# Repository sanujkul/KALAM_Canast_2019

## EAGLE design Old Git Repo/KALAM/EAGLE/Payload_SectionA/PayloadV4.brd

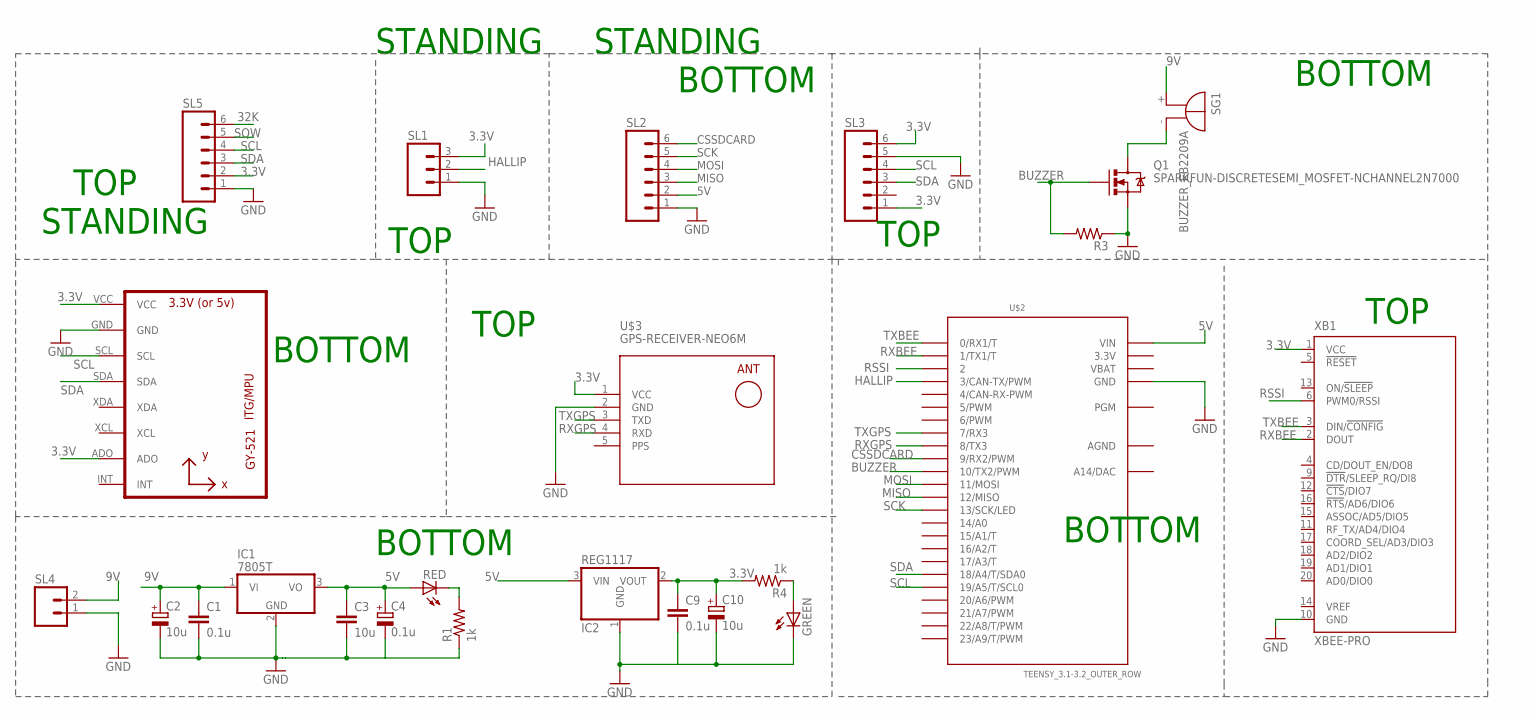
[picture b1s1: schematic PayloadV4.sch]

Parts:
C1, C9: 0.1u; C025-025X050
C2, C10: 10u; E2,5-6
C3: 10u; C025-025X050
C4: 0.1u; E2,5-6
GREEN: red; LED3MM
IC1: 7805T; TO220H
IC2: REG1117; SOT223
Q1: SPARKFUN-DISCRETESEMI_MOSFET-NCHANNEL2N7000; SPARKFUN-DISCRETESEMI_TO-92
R1, R4: 1k; 0204/7
R3: R-US_0204/7; 0204/7
RED: red; LED3MM
SG1: BUZZER_EB2209A
SL1: M03; 03P
SL2, SL3, SL5: M06; 06P
SL4: M02; 02P
U1: GY-521MPU6050; GY-521
U$2: TEENSY_3.1-3.2_OUTER_ROW; TEENSY_3.0-3.2&LC_OUTER_ROW
U$3: GPS-RECEIVER-NEO6M
XB1: XBEE-PRO

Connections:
3.3V: C9.1, C10.+, IC2.2 (VOUT), R4.2, SL1.3, SL3.1, SL3.6, SL5.2, U1.ADO, U1.VCC, U$2.3.3V, U$2.3.3V1 (3.3V), U$3.1 (VCC), XB1.1 (VCC)
5V: C3.1, C4.+, IC1.3 (VO), IC2.3 (VIN), RED.A, SL2.2, U$2.VIN
9V: C1.1, C2.+, IC1.1 (VI), SG1.+, SL4.2
32K: SL5.6
AGND: U$2.AGND
BUZZER: Q1.2 (G), R3.2, U$2.10 (10/TX2/PWM)
CSSDCARD: SL2.6, U$2.9 (9/RX2/PWM)
GND: C1.2, C2.-, C3.2, C4.-, C9.2, C10.-, GREEN.K (C), IC1.2 (GND), IC2.1 (GND), Q1.1 (S), R1.1, R3.1, SL1.1, SL2.1, SL3.5, SL4.1, SL5.1, U1.GND, U$2.GND, U$2.GND1 (GND), U$3.2 (GND), XB1.10 (GND)
HALLIP: SL1.2, U$2.3 (3/CAN-TX/PWM)
MISO: SL2.3, U$2.12 (12/MISO)
MOSI: SL2.4, U$2.11 (11/MOSI)
unnamed: R1.2, RED.K (C)
unnamed: GREEN.A, R4.1
unnamed: Q1.3 (D), SG1.-
PPS: U$3.5 (PPS)
RSSI: U$2.2, XB1.6 (PWM0/RSSI)
RXBEE: U$2.1 (1/TX1/T), XB1.2 (DOUT)
RXGPS: U$2.8 (8/TX3), U$3.4 (RXD)
SCK: SL2.5, U$2.13 (13/SCK/LED)
SCL: SL3.4, SL5.4, U1.SCL, U$2.19/A5 (19/A5/T/SCL0)
SDA: SL3.3, SL5.3, U1.SDA, U$2.18/A4 (18/A4/T/SDA0)
SQW: SL5.5
TXBEE: U$2.0 (0/RX1/T), XB1.3 (DIN/!CONFIG)
TXGPS: U$2.7 (7/RX3), U$3.3 (TXD)
VBAT: U$2.VBAT

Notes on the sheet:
TOP
BOTTOM
STANDING

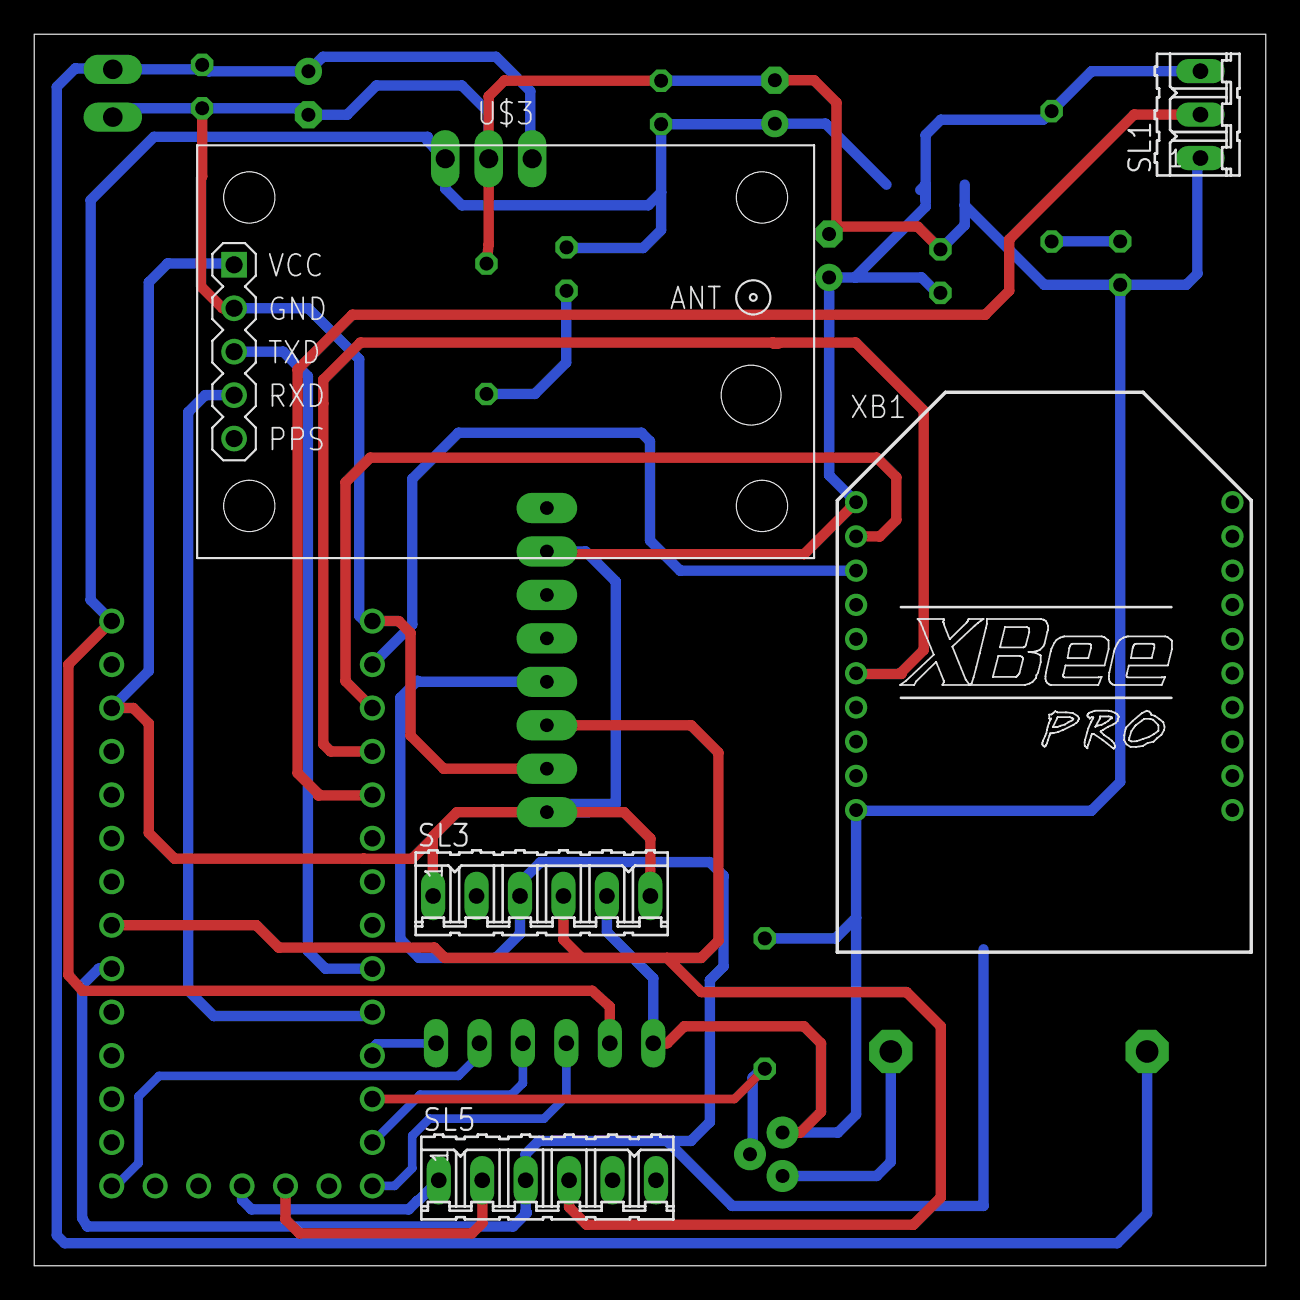
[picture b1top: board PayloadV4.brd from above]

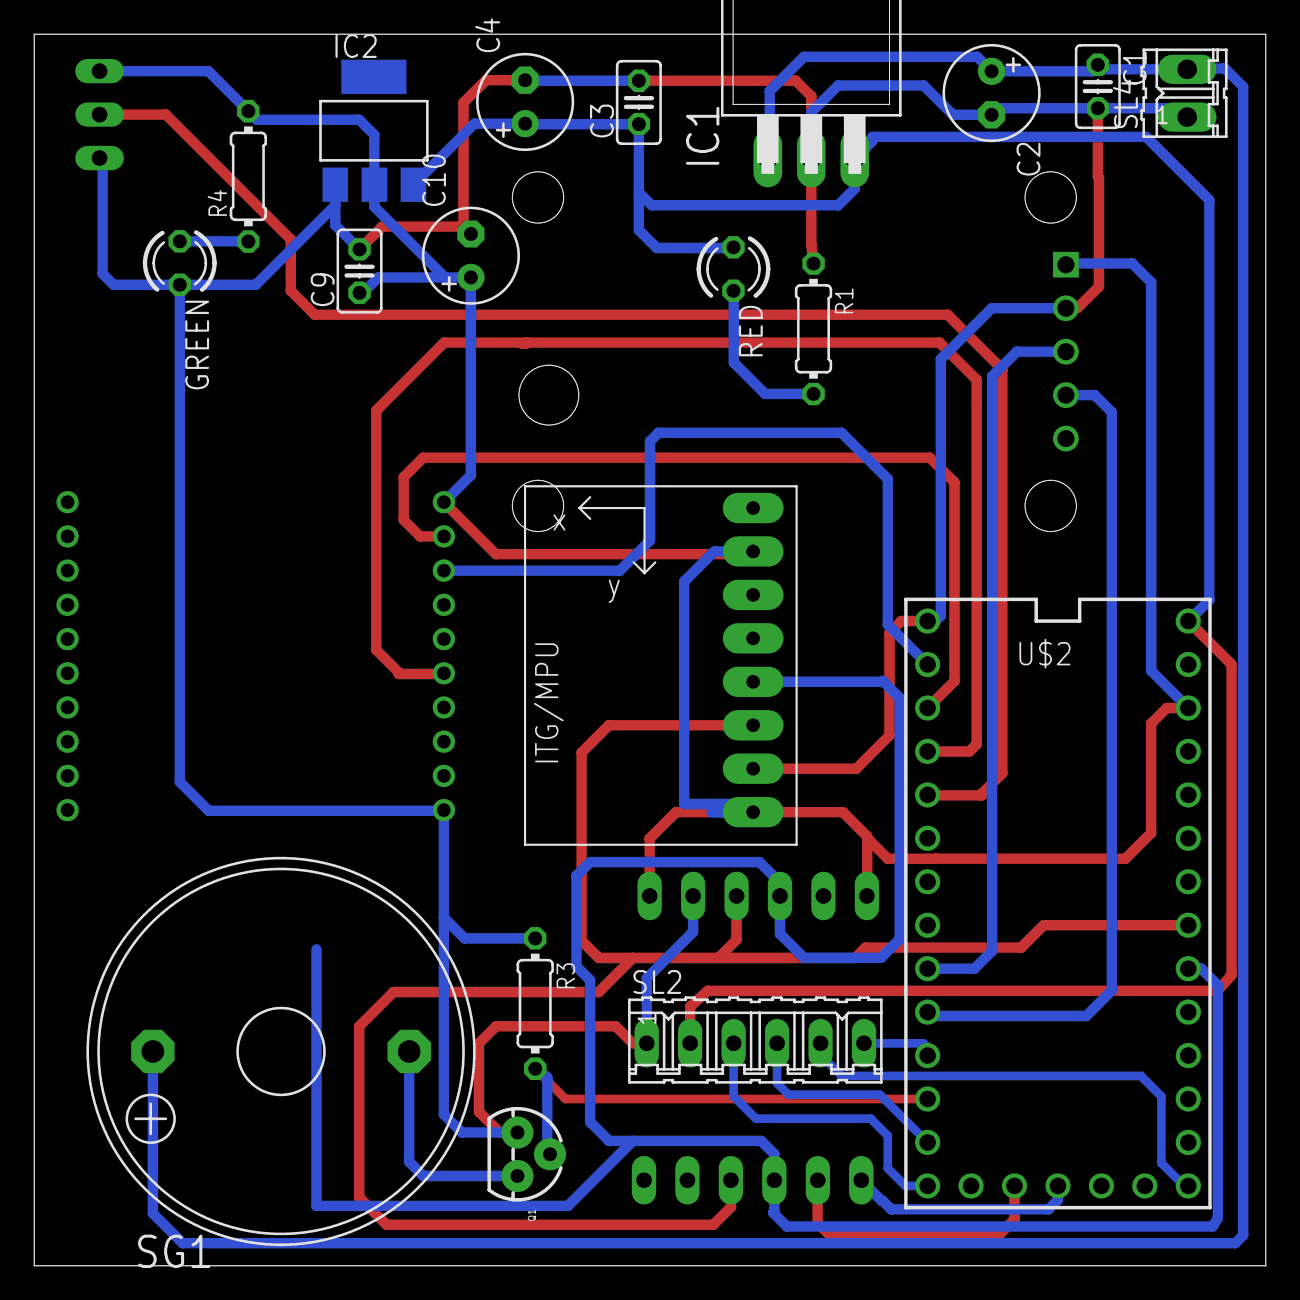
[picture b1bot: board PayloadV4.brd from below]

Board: 2 copper layers, 72.0 x 72.0 mm, 24 parts (19 on the bottom side), 20 nets.

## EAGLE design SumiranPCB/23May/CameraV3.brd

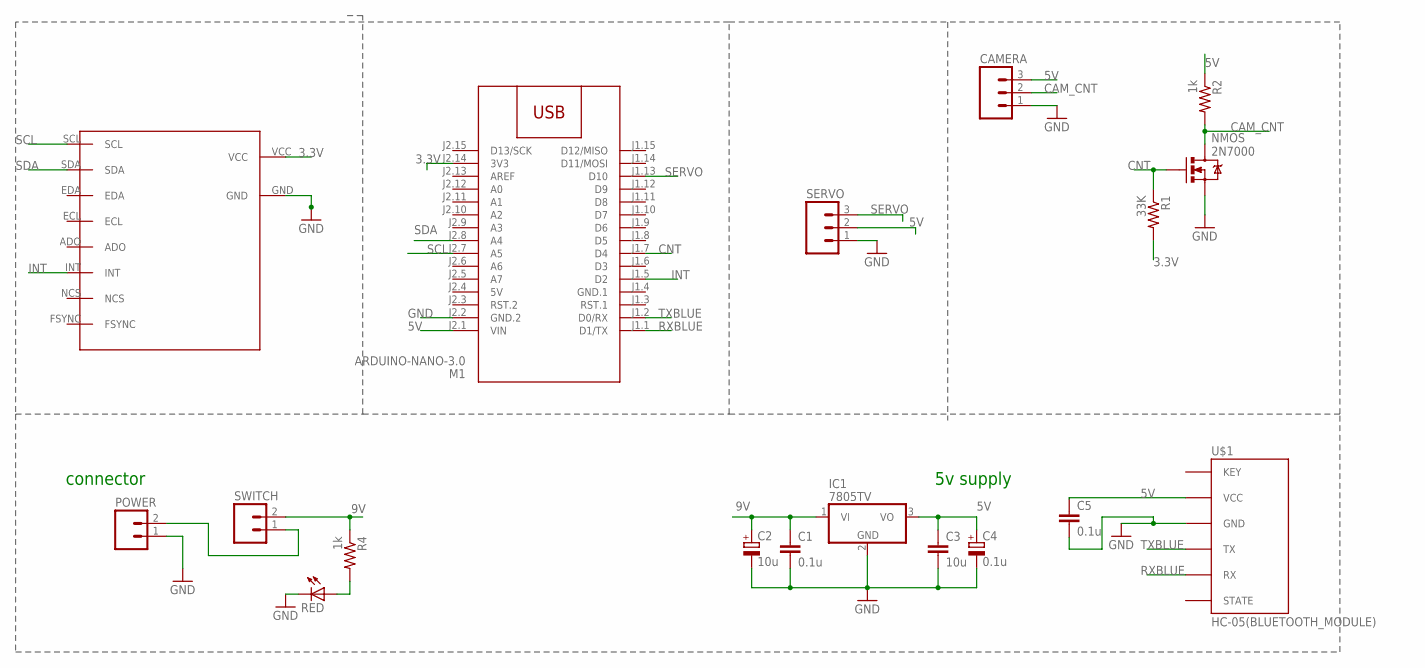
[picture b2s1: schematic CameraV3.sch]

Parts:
C1, C5: 0.1u; C025-025X050
C2: 10u; E2,5-6
C3: 10u; C025-025X050
C4: 0.1u; E2,5-6
CAMERA: CON-AMP-QUICK_M03; CON-AMP-QUICK_03P
IC1: 7805TV; TO220V
M1: ARDUINO-NANO-3.0
POWER: CEDT_JANUARY_2015_V5_M02; CEDT_JANUARY_2015_V5_02P
Q1: SPARKFUN-DISCRETESEMI_MOSFET-NCHANNEL2N7000; SPARKFUN-DISCRETESEMI_TO-92
R1: 33K; 0204/7
R2, R4: 1k; 0204/7
RED: red; LED3MM
SERVO: CON-AMP-QUICK_M03; CON-AMP-QUICK_03P
SWITCH: M02; 02P
U$1: HC-05(BLUETOOTH_MODULE); HC-05
U$2: MPU9250

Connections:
3.3V: M1.J2.14 (3V3), R1.2, U$2.VCC
5V: C3.1, C4.+, C5.1, CAMERA.3, IC1.3 (VO), M1.J2.1 (VIN), M1.J2.4 (5V), R2.1, SERVO.2, U$1.VCC
9V: C1.1, C2.+, IC1.1 (VI), R4.1, SWITCH.2
CAM_CNT: CAMERA.2, Q1.3 (D), R2.2
CNT: M1.J1.7 (D4), Q1.2 (G), R1.1
GND: C1.2, C2.-, C3.2, C4.-, C5.2, CAMERA.1, IC1.2 (GND), M1.J2.2 (GND.2), POWER.1, Q1.1 (S), RED.K (C), SERVO.1, U$1.GND, U$2.GND
GND.1: M1.J1.4 (GND.1)
INT: M1.J1.5 (D2), U$2.INT
unnamed: POWER.2, SWITCH.1
unnamed: R4.2, RED.A
RXBLUE: M1.J1.1 (D1/TX), U$1.RX
SCL: M1.J2.7 (A5), U$2.SCL
SDA: M1.J2.8 (A4), U$2.SDA
SERVO: M1.J1.13 (D10), SERVO.3
TXBLUE: M1.J1.2 (D0/RX), U$1.TX

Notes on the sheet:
connector
5v supply

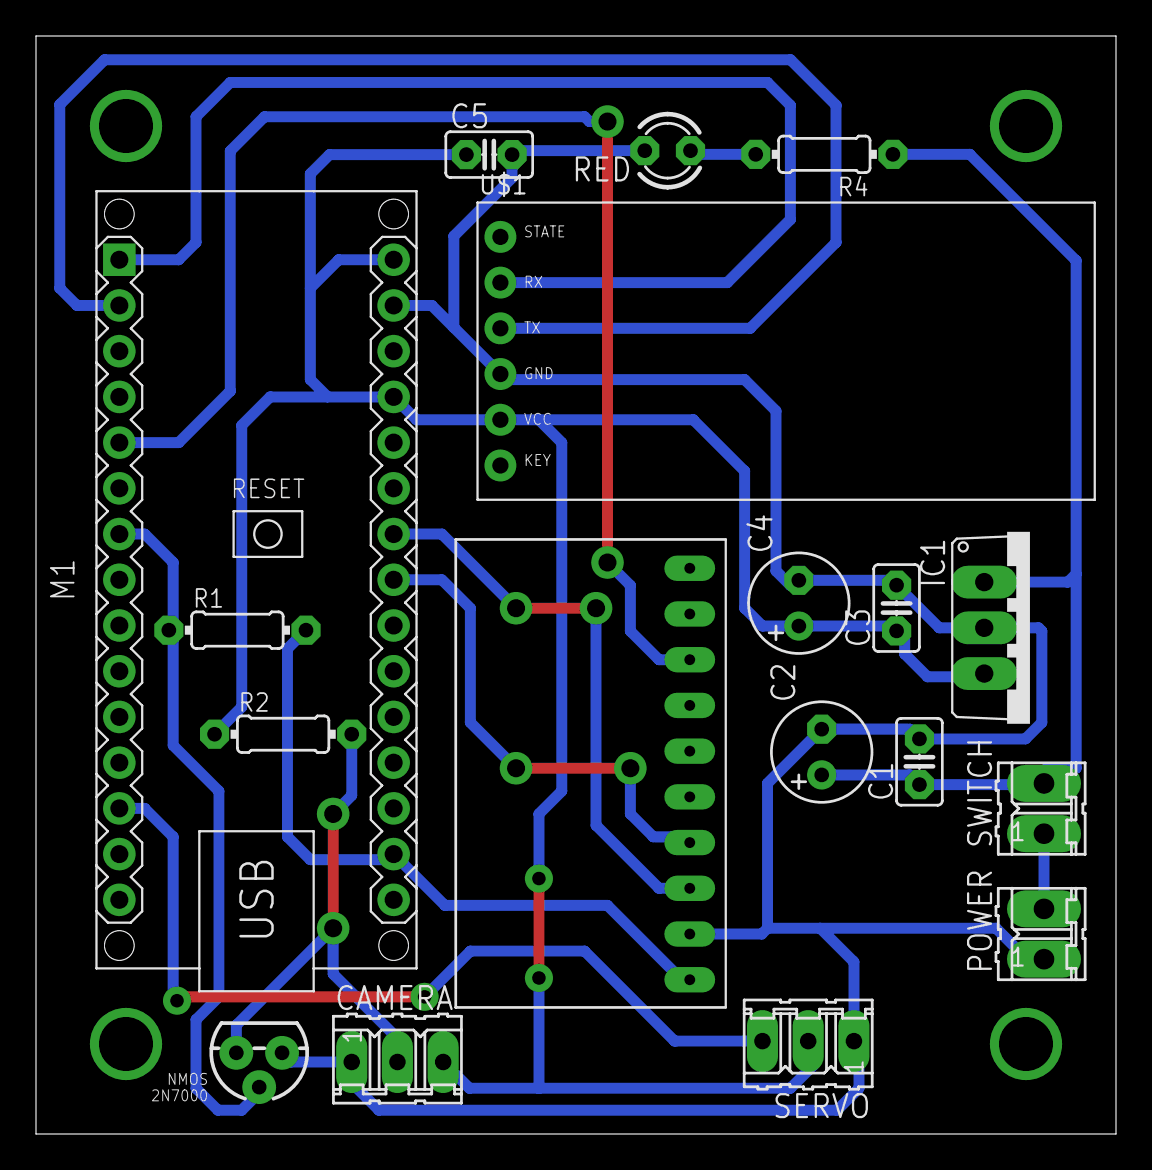
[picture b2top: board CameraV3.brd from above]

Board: 2 copper layers, 60.0 x 61.0 mm, 18 parts (0 on the bottom side), 14 nets.

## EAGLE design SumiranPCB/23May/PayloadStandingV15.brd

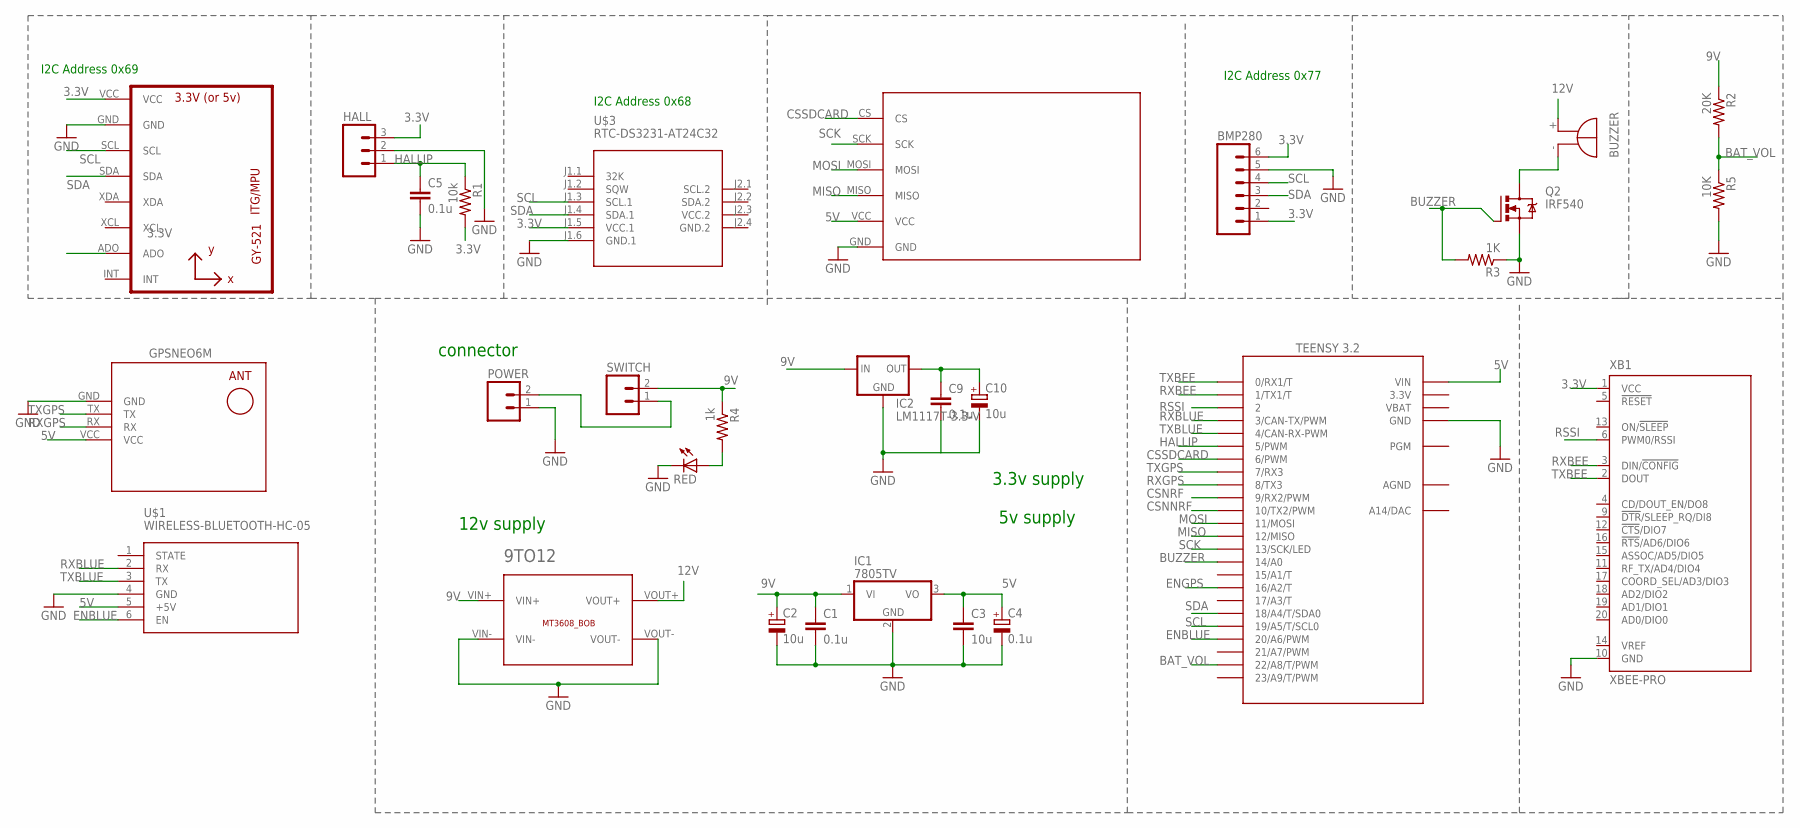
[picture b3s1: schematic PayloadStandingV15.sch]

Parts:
9TO12: BREAKOUTS_MT3608_BOB
BMP280: M06; 06P
C1, C5, C9: 0.1u; C025-025X050
C2, C10: 10u; E2,5-6
C3: 10u; C025-025X050
C4: 0.1u; E2,5-6
HALL: M03; 03P
IC1: 7805TV; TO220V
IC2: LM1117T-3.3-V; TO220V
POWER: CEDT_JANUARY_2015_V5_M02; CEDT_JANUARY_2015_V5_02P
Q2: IRF540; TO220BV
R1: 10k; 0204/7
R2: 20K; 0204/7
R3: 1K; 0204/7
R4: 1k; 0204/7
R5: 10K; 0204/7
RED: red; LED3MM
SG1: BUZZER_EB2209A
SWITCH: M02; 02P
U1: GY-521MPU6050; GY-521
U$1: WIRELESS-BLUETOOTH-HC-05
U$2: TEENSY_3.1-3.2_OUTER_ROW; TEENSY_3.0-3.2&LC_OUTER_ROW
U$3: RTC-DS3231-AT24C32
U$4: GPS-RECEIVER-NEO6M
U$5: SDCARD; M0SDCARDMODULE
XB1: XBEE-PRO

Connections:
3.3V: BMP280.1, BMP280.6, C9.1, C10.+, HALL.3, IC2.2 (OUT), R1.2, U1.ADO, U1.VCC, U$2.3.3V, U$2.3.3V1 (3.3V), U$3.J1.5 (VCC.1), XB1.1 (VCC)
5V: C3.1, C4.+, IC1.3 (VO), U$1.5 (+5V), U$2.VIN, U$4.VCC, U$5.VCC
9V: 9TO12.VIN+, C1.1, C2.+, IC1.1 (VI), IC2.3 (IN), R2.1, R4.1, SWITCH.2
12V: 9TO12.VOUT+, SG1.+
AGND: U$2.AGND
BAT_VOL: R2.2, R5.1, U$2.22/A8 (22/A8/T/PWM)
BUZZER: Q2.G, R3.2, U$2.14/A0
CSNNRF: U$2.10 (10/TX2/PWM)
CSNRF: U$2.9 (9/RX2/PWM)
CSSDCARD: U$2.6 (6/PWM), U$5.CS
ENBLUE: U$1.6 (EN), U$2.20/A6 (20/A6/PWM)
ENGPS: U$2.16/A2 (16/A2/T)
GND: 9TO12.VIN-, 9TO12.VOUT-, BMP280.5, C1.2, C2.-, C3.2, C4.-, C5.2, C9.2, C10.-, HALL.2, IC1.2 (GND), IC2.1 (GND), POWER.1, Q2.S, R3.1, R5.2, RED.K (C), U1.GND, U$1.4 (GND), U$2.GND, U$2.GND1 (GND), U$3.J1.6 (GND.1), U$4.GND, U$5.GND, XB1.10 (GND)
GND.2: U$3.J2.4 (GND.2)
HALLIP: C5.1, HALL.1, R1.1, U$2.5 (5/PWM)
MISO: U$2.12 (12/MISO), U$5.MISO
MOSI: U$2.11 (11/MOSI), U$5.MOSI
unnamed: POWER.2, SWITCH.1
unnamed: R4.2, RED.A
unnamed: Q2.D, SG1.-
RSSI: U$2.2, XB1.6 (PWM0/RSSI)
RXBEE: U$2.1 (1/TX1/T), XB1.3 (DIN/!CONFIG)
RXBLUE: U$1.2 (RX), U$2.3 (3/CAN-TX/PWM)
RXGPS: U$2.8 (8/TX3), U$4.RX
SCK: U$2.13 (13/SCK/LED), U$5.SCK
SCL: BMP280.4, U1.SCL, U$2.19/A5 (19/A5/T/SCL0), U$3.J1.3 (SCL.1)
SDA: BMP280.3, U1.SDA, U$2.18/A4 (18/A4/T/SDA0), U$3.J1.4 (SDA.1)
TXBEE: U$2.0 (0/RX1/T), XB1.2 (DOUT)
TXBLUE: U$1.3 (TX), U$2.4 (4/CAN-RX-PWM)
TXGPS: U$2.7 (7/RX3), U$4.TX
VBAT: U$2.VBAT
VCC.2: U$3.J2.3 (VCC.2)

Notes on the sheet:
connector
3.3v supply
5v supply
12v supply
I2C Address 0x77
I2C Address 0x68
I2C Address 0x69

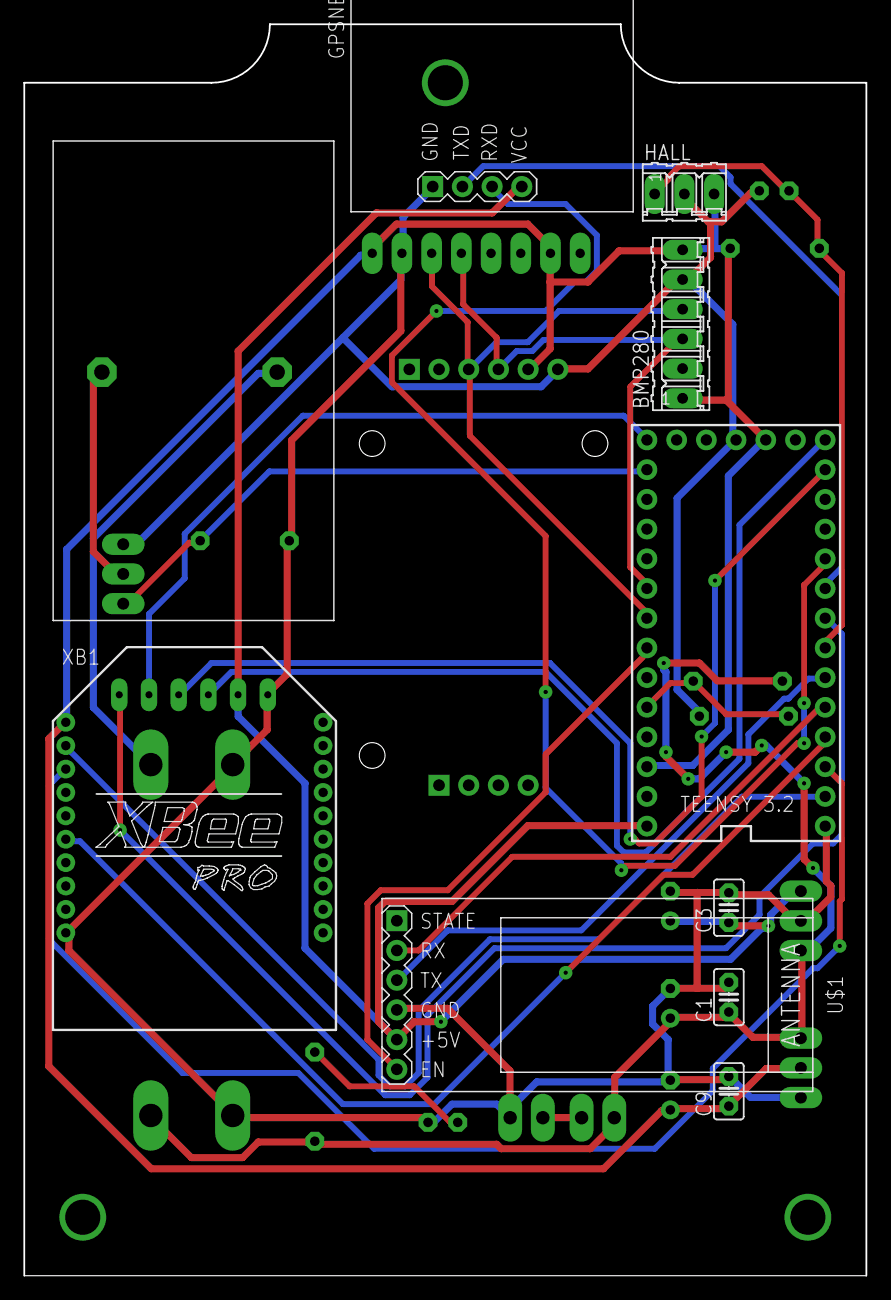
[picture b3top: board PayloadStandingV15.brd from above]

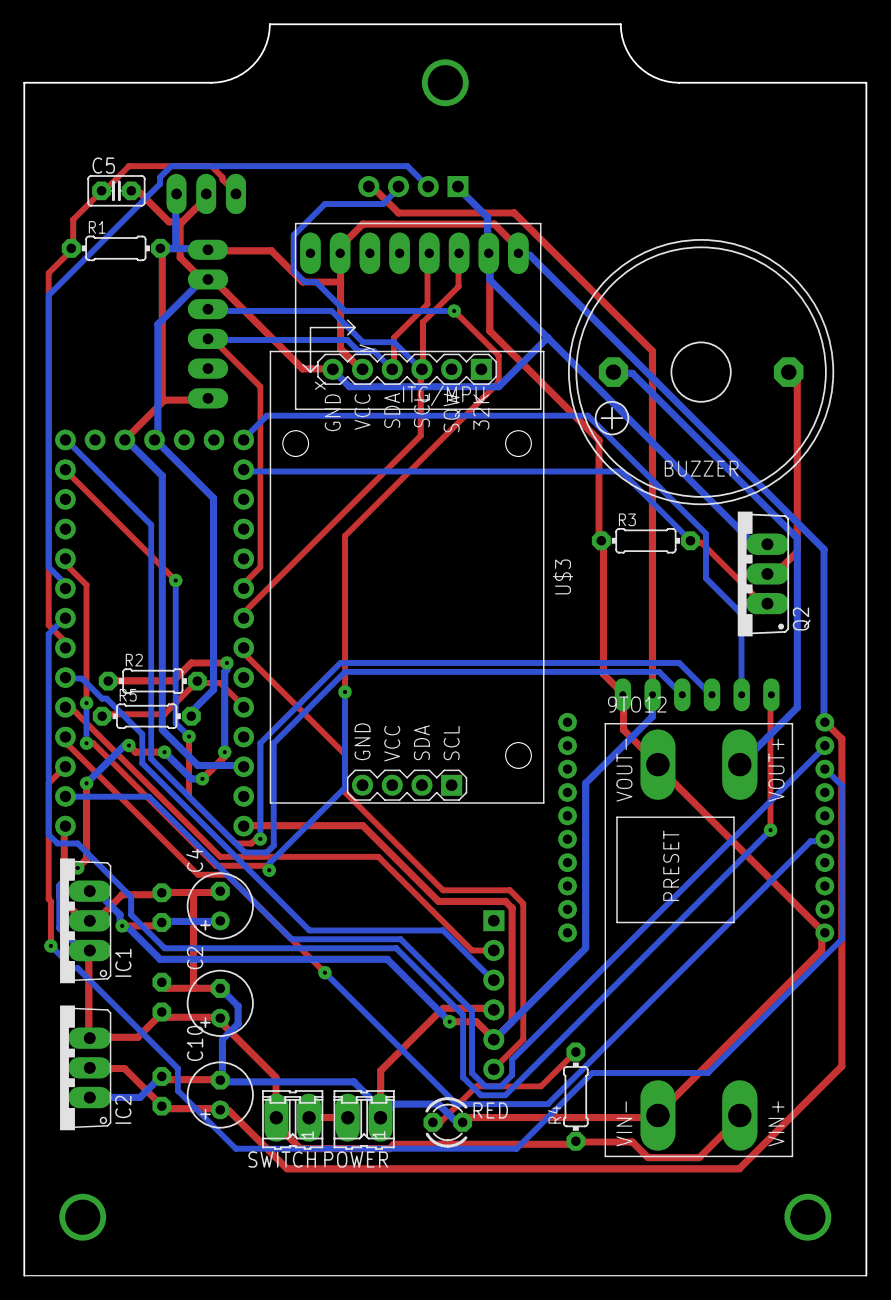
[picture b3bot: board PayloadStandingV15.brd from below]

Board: 2 copper layers, 72.0 x 107.0 mm, 29 parts (19 on the bottom side), 25 nets.

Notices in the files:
parts and their libraries:
diy-modules: Released under the Creative Commons Attribution 4.0 International License: http://creativecommons.org/licenses/by/4.0
